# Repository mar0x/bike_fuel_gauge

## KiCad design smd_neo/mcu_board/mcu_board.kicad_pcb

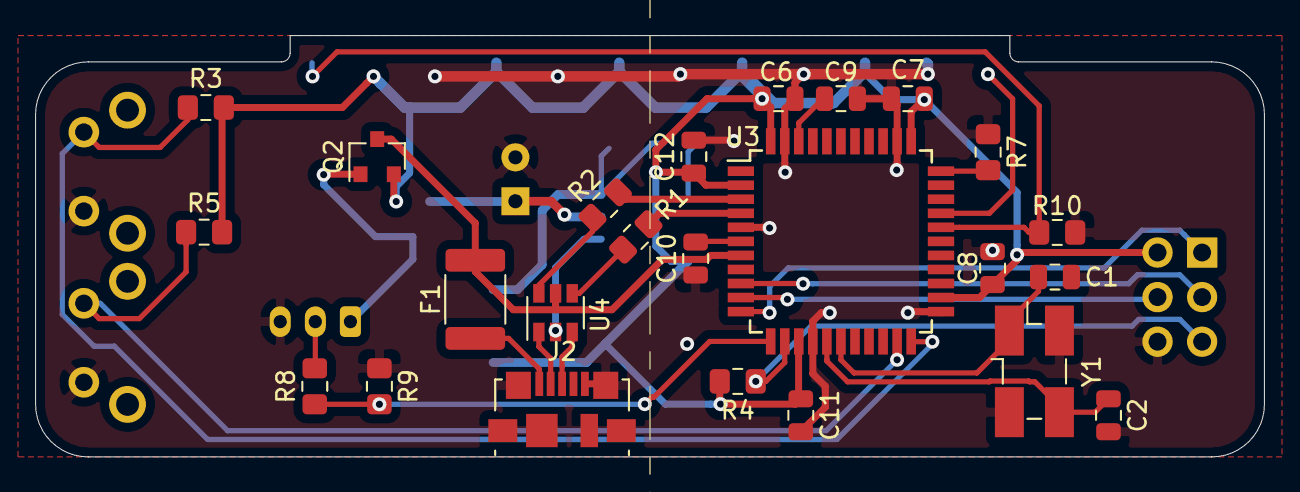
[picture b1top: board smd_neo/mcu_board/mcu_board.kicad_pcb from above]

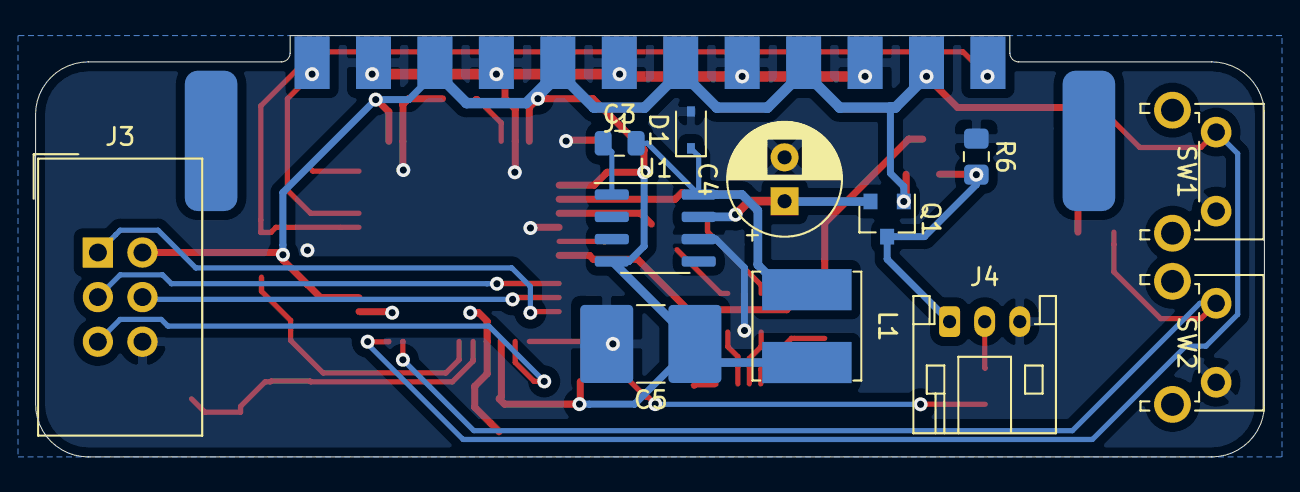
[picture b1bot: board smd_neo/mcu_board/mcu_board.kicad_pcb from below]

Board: 2 copper layers, 70.0 x 24.0 mm, 37 parts (13 on the bottom side), 29 nets.

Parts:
C1, C2: 22pF; C_0805_2012Metric
C3: 10nF; C_0805_2012Metric
C4: 100uF; CP_Radial_D6.3mm_P2.50mm
C5: 68uF; C_2816_7142Metric
C6, C7, C8, C9, C11, C12: 0.1uF; C_0805_2012Metric
C10: 1uF; C_0805_2012Metric
D1: D_Schottky; D_SOD-323
F1: Polyfuse_Small; Fuse_1812_4532Metric_Pad1.30x3.40mm_HandSolder
J1: Conn_01x12_Male; PCBEdge_x12
J2: USB_B_Micro; USB_Micro-B_Molex_47346-0001
J3: Conn_02x03_Odd_Even; IDC-Header_2x03_P2.54mm_Vertical
J4: Conn_01x03_Male; JST_PH_S3B-PH-K_1x03_P2.00mm_Horizontal
L1: 47uH; L_Bourns_SRN6045TA
Q1, Q2: BSS84; SOT-23
R1, R2: 22; R_0805_2012Metric_Pad1.15x1.40mm_HandSolder
R3, R5, R10: 47k; R_0805_2012Metric_Pad1.15x1.40mm_HandSolder
R4, R7: 10k; R_0805_2012Metric_Pad1.15x1.40mm_HandSolder
R6, R8: 100k; R_0805_2012Metric_Pad1.15x1.40mm_HandSolder
R9: 50k; R_0805_2012Metric_Pad1.15x1.40mm_HandSolder
SW1, SW2: SW_Push; SW_Tactile_SPST_Angled_PTS645Vx58-2LFS
U1: LM2675M-5; SOIC-8_3.9x4.9mm_P1.27mm
U3: ATmega32U4-AU; TQFP-44_10x10mm_P0.8mm
U4: USBLC6-2SC6; SOT-23-6
Y1: Crystal_GND24_Small; Crystal_SMD_EuroQuartz_MJ-4Pin_5.0x3.2mm_HandSoldering

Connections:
+5V: C5.1, C6.2, C7.2, C8.2, C11.1, C12.1, J1.3, J1.5, J1.7, J1.9, J1.11, J3.2, L1.2, Q1.1, Q2.2, R3.2, R4.2, R5.2, U1.4, U3.2, U3.14, U3.24, U3.34, U3.44
+12V: J4.1, Q1.3, Q2.1, R6.2
D+: R1.1, U3.4
D-: R2.1, U3.3
GND: C1.2, C2.2, C4.2, C5.2, C6.1, C7.1, C8.1, C9.1, C10.1, C11.2, C12.2, D1.2, J1.2, J1.4, J1.6, J1.8, J1.10, J2.5, J2.6, J3.6, J4.3, R6.1, R7.1, R9.1, R10.1, SW1.2, SW2.2, U1.6, U3.5, U3.15, U3.23, U3.35, U3.43, U4.2, Y1.2, Y1.4
MISO: J3.1, U3.11
MOSI: J3.4, U3.10
NEO: J1.1, U3.30
unnamed: C1.1, U3.17, Y1.1
unnamed: C2.1, U3.16, Y1.3
unnamed: C3.1, U1.1
unnamed: C3.2, D1.1, L1.1, U1.8
unnamed: C4.1, Q1.2, U1.7
unnamed: C9.2, U3.42
unnamed: C10.2, U3.6
unnamed: F1.2, J2.1
unnamed: J2.2, U4.1
unnamed: J2.3, U4.3
unnamed: J4.2, R8.2
unnamed: R1.2, U4.4
unnamed: R2.2, U4.6
unnamed: R7.2, U3.33
ROPT: J1.12, R10.2, U3.29
SCK: J3.3, U3.9
SENSOR: R8.1, R9.2, U3.12
SW1: R3.1, SW1.1, U3.22
SW2: R5.1, SW2.1, U3.21
VBUS: F1.1, Q2.3, U3.7, U4.5
~RST: J3.5, R4.1, U3.13

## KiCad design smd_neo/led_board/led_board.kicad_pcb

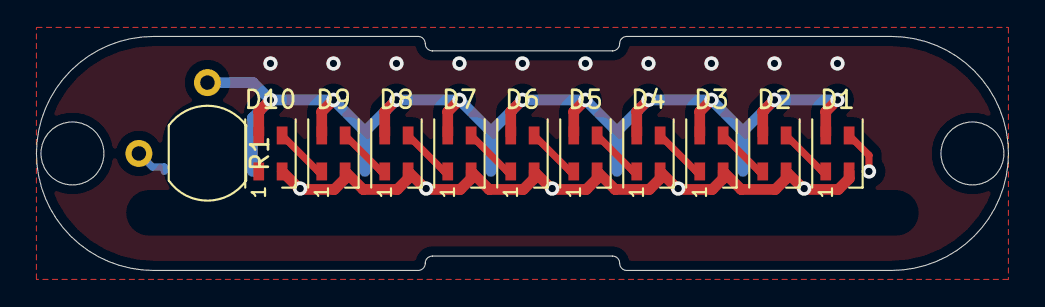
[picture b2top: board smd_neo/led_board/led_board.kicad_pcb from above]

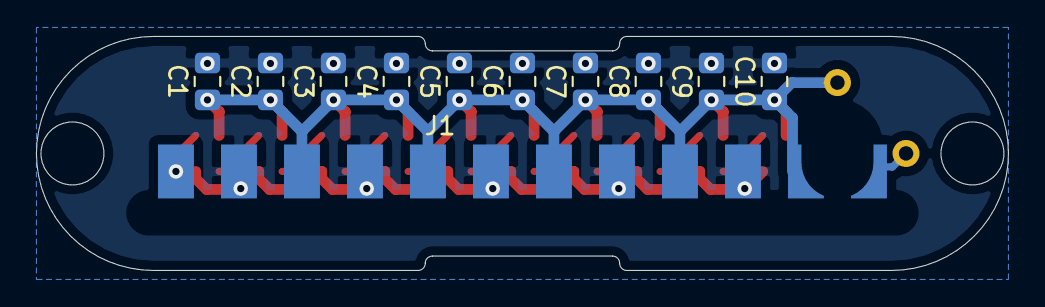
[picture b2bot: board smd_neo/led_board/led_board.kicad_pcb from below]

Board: 2 copper layers, 54.0 x 13.0 mm, 25 parts (11 on the bottom side), 13 nets.

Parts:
C1, C2, C3, C4, C5, C6, C7, C8, C9, C10: 0.1uF; C_0805_2012Metric_Pad1.15x1.40mm_HandSolder
D1, D2, D3, D4, D5, D6, D7, D8, D9, D10: SK6805; LED_SK6805_PLCC4_2.4x2.7mm_P1.3mm
H1: MountingHole; MCUBoardHole
H2, H3: MountingHole; MountingHole_3.5mm
J1: Conn_01x12_Male; PCBEdge_x12
R1: R_PHOTO; R_LDR_5.1x4.3mm_P3.4mm_Vertical

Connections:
+5V: C1.1, C2.1, C3.1, C4.1, C5.1, C6.1, C7.1, C8.1, C9.1, C10.1, D1.4, D2.4, D3.4, D4.4, D5.4, D6.4, D7.4, D8.4, D9.4, D10.4, J1.3, J1.5, J1.7, J1.9, J1.11, R1.1
DIN: D1.3, J1.1
GND: C1.2, C2.2, C3.2, C4.2, C5.2, C6.2, C7.2, C8.2, C9.2, C10.2, D1.2, D2.2, D3.2, D4.2, D5.2, D6.2, D7.2, D8.2, D9.2, D10.2, J1.2, J1.4, J1.6, J1.8, J1.10
unnamed: D1.1, D2.3
unnamed: D2.1, D3.3
unnamed: D3.1, D4.3
unnamed: D4.1, D5.3
unnamed: D5.1, D6.3
unnamed: D6.1, D7.3
unnamed: D7.1, D8.3
unnamed: D8.1, D9.3
unnamed: D9.1, D10.3
ROUT: J1.12, R1.2

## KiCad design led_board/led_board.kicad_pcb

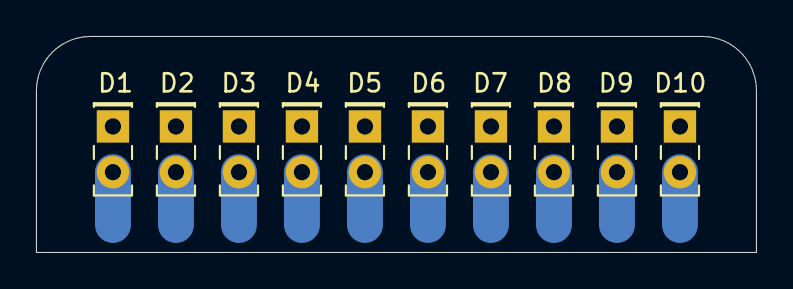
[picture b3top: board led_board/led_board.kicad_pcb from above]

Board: 2 copper layers, 40.0 x 12.0 mm, 11 parts (1 on the bottom side), 11 nets.

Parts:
D1, D2, D3, D4, D5, D6, D7, D8, D9, D10: LED; LED_Rectangular_W5.0mm_H2.0mm
J1: Conn_01x11_Male; PCBEdge_x11

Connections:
GND: D1.1, D2.1, D3.1, D4.1, D5.1, D6.1, D7.1, D8.1, D9.1, D10.1, J1.11
unnamed: D1.2, J1.1
unnamed: D2.2, J1.2
unnamed: D3.2, J1.3
unnamed: D4.2, J1.4
unnamed: D5.2, J1.5
unnamed: D6.2, J1.6
unnamed: D7.2, J1.7
unnamed: D8.2, J1.8
unnamed: D9.2, J1.9
unnamed: D10.2, J1.10

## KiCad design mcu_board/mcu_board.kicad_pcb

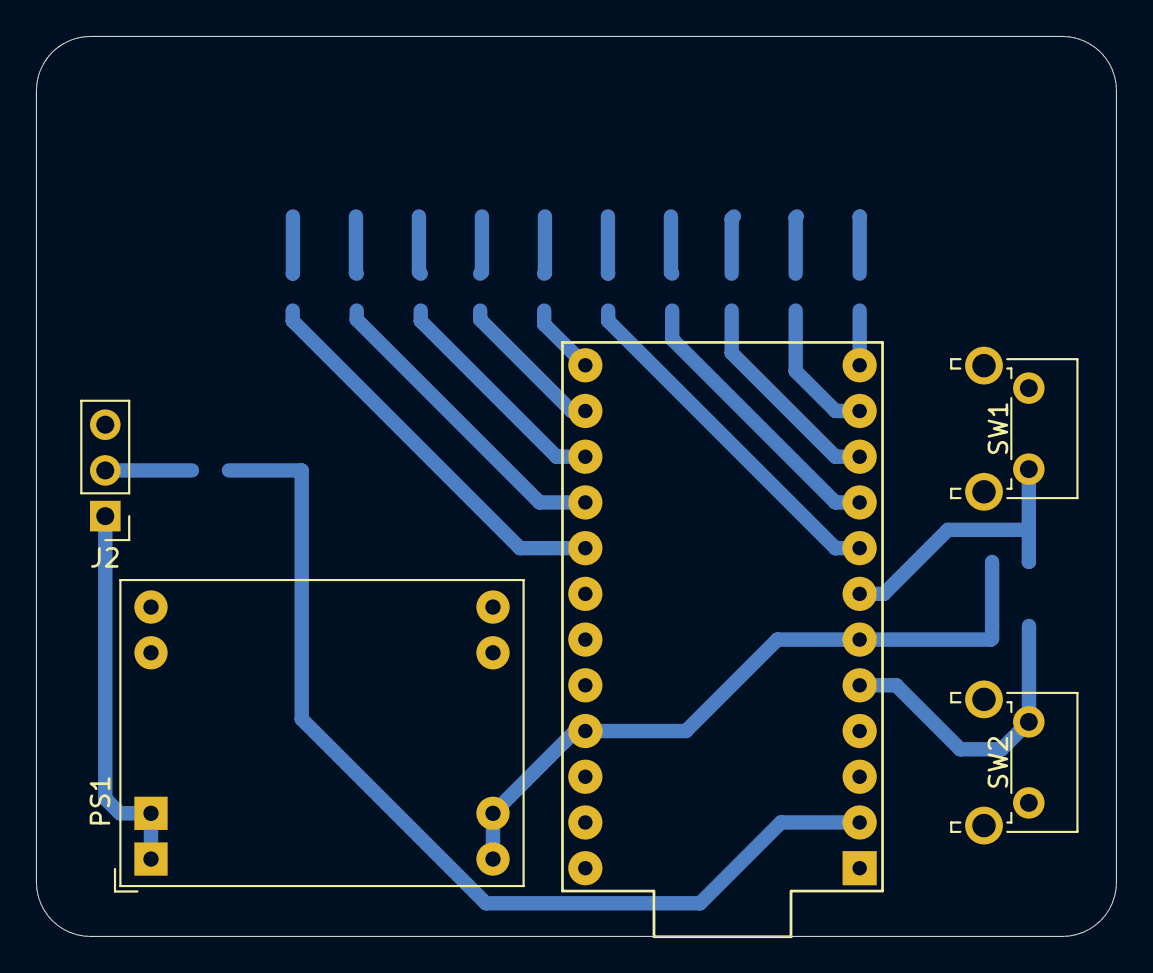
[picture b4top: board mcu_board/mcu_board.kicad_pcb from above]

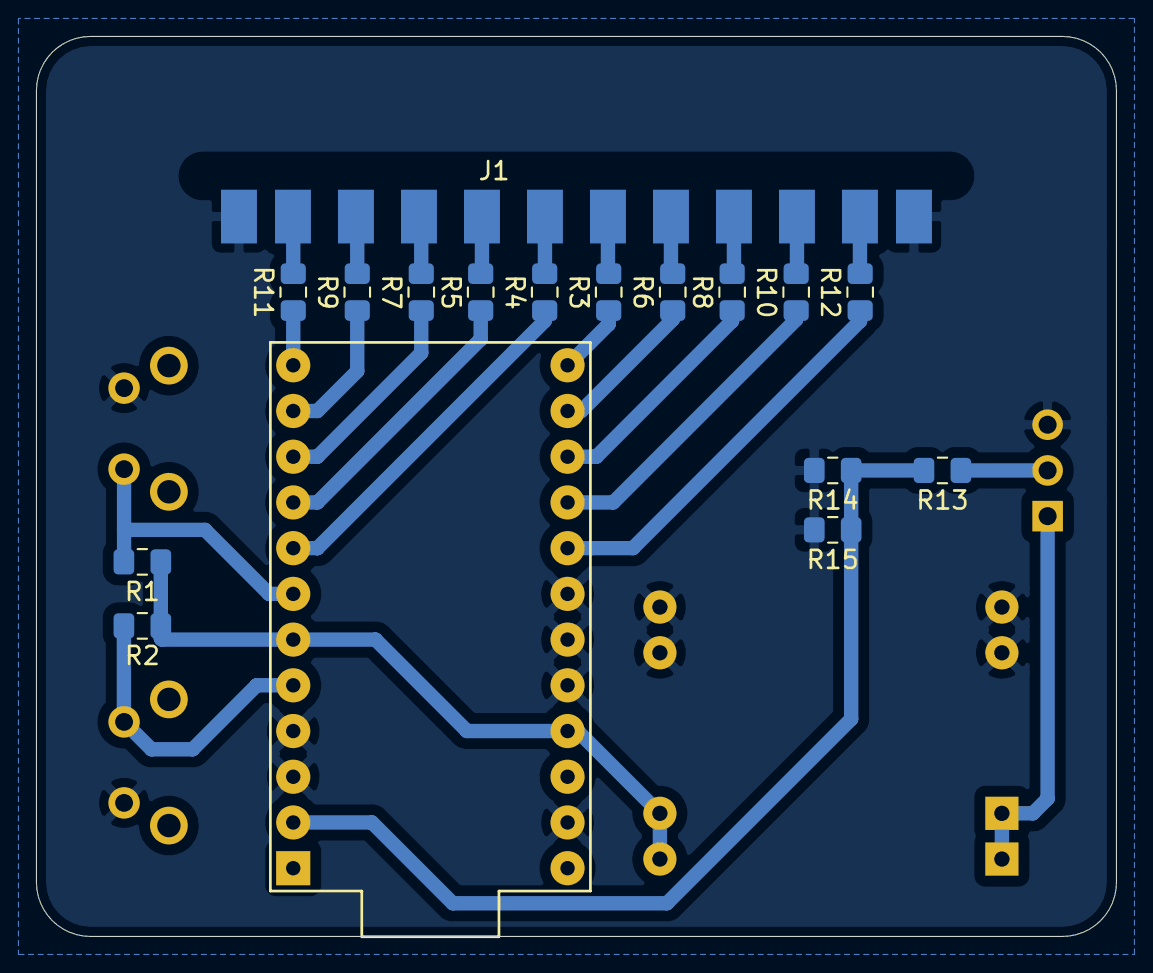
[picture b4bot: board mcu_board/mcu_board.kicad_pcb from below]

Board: 2 copper layers, 60.0 x 50.0 mm, 21 parts (16 on the bottom side), 27 nets.

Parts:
J1: Conn_01x11_Male; PCBEdge_x11
J2: Conn_01x03_Male; PinHeader_1x03_P2.54mm_Vertical
PS1: D-SUN; Converter_DCDC_D_SUN_THT
R1, R2: 39k; R_0805_2012Metric_Pad1.15x1.40mm_HandSolder
R3, R4, R5, R6, R7, R8, R9, R10, R11, R12: 330; R_0805_2012Metric_Pad1.15x1.40mm_HandSolder
R13, R14, R15: 100k; R_0805_2012Metric_Pad1.15x1.40mm_HandSolder
SW1, SW2: SW_Push; SW_Tactile_SPST_Angled_PTS645Vx58-2LFS
U1: ProMicro

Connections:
+5V: PS1.3, R1.1, R2.1, U1.6, U1.21
+12V: J2.1, PS1.1
EMPTY: R1.2, SW1.2, U1.7
FULL: R2.2, SW2.1, U1.5
GND: J1.11, J2.3, PS1.2, PS1.4, R14.2, R15.2, SW1.1, SW2.2, U1.3, U1.4, U1.18, U1.19, U1.20, U1.23
LED1: J1.1, R11.2
LED2: J1.2, R9.2
LED3: J1.3, R7.2
LED4: J1.4, R5.2
LED5: J1.5, R4.2
LED6: J1.6, R3.2
LED7: J1.7, R6.2
LED8: J1.8, R8.2
LED9: J1.9, R10.2
LED10: J1.10, R12.2
unnamed: J2.2, R13.1
unnamed: R3.1, U1.13
unnamed: R4.1, U1.8
unnamed: R5.1, U1.9
unnamed: R6.1, U1.14
unnamed: R7.1, U1.10
unnamed: R8.1, U1.15
unnamed: R9.1, U1.11
unnamed: R10.1, U1.16
unnamed: R11.1, U1.12
unnamed: R12.1, U1.17
SENSOR: R13.2, R14.1, R15.1, U1.2

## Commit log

2020-07-30 Updating gitignore
2020-07-30 PCB and firmware for Pro sensor
2020-07-30 Minor fixes
2020-08-03 Level configuration
2020-08-03 Noise filter
2020-09-10 Dimensions added
2020-09-10 Debug level changed, start_intro() introduced.
2021-05-19 Introducing FuelGauge board package
2021-05-19 Adding firmware for NEO-pixel board
2021-05-19 Adding NEO-pixel based board(s).
2021-05-19 Fixing misprint
